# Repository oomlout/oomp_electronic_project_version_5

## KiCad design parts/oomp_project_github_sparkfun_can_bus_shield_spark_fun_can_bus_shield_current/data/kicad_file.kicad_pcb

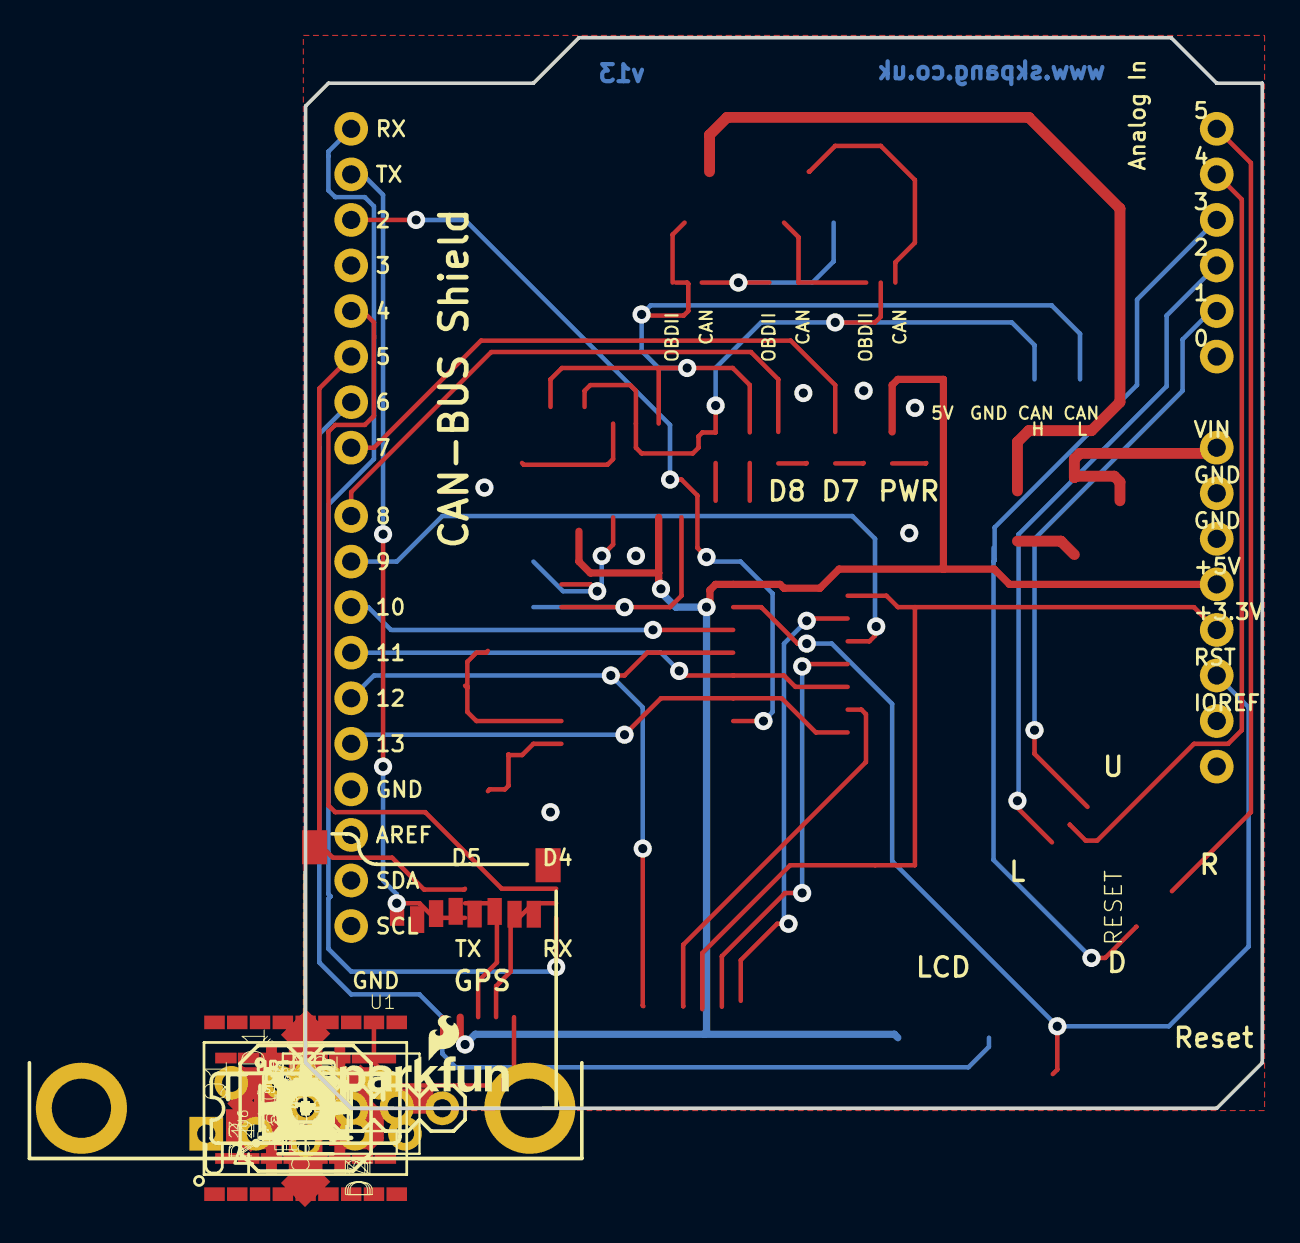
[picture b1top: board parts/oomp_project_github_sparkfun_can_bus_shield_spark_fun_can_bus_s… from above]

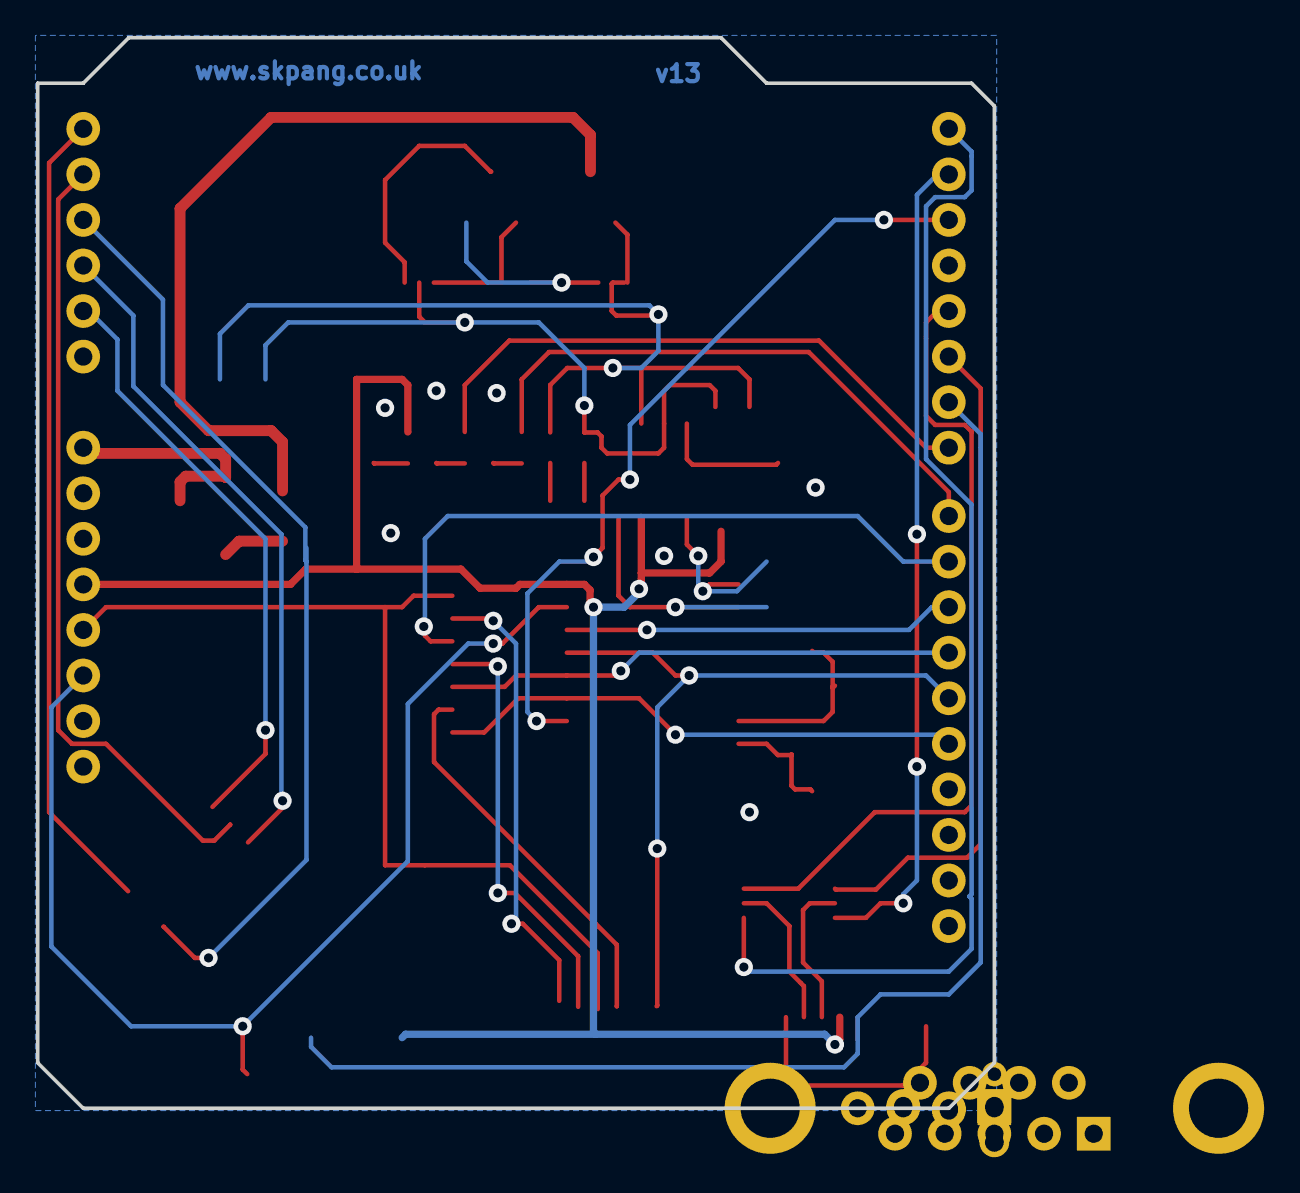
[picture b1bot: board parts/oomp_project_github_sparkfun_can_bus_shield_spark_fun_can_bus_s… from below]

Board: 2 copper layers, 53.3 x 59.7 mm, 48 parts (2 on the bottom side), 47 nets.

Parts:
C1, C6, C8: 0.1uF; 0603-CAP
C2, C3: 560pF; 0603-CAP
C4: 4.7uF; 0603-CAP
C5, C7: 22pF; 0603-CAP
C9: 1.0uF; 0603-CAP
D1: MBRA140; SMA-DIODE
D2, D3: GREEN; LED-0603
D4: RED; LED-0603
D5: PESD1CAN; SOT23-3
F1: PTC-1206
FRAME1: FRAME-LETTER; CREATIVE_COMMONS
FRAME2: FRAME-LETTERNO_PACKAGE; DUMMY
JP1: DNP; MOLEX-1X3_LOCK
JP2, JP3: FIDUCIAL1X2; FIDUCIAL-1X2
JP4: SFE_LOGO_NAME_FLAME.1_INCH; SFE_LOGO_NAME_FLAME_.1
JP5: DNP; 1X04
LOGO1: OSHW-LOGOM; OSHW-LOGO-M
Q1: 16MHz; CRYSTAL-SMD-5X3
R1, R2, R3: 1K; 0603-RES
R10, R12: 100; 0603-RES
R13: 4.7K; 0603-RES
S2: RESET; TACTILE-SWITCH-SMD
SJ1, SJ2, SJ4, SJ5, SJ6: JUMPER-PAD-3-2OF3_NC_BY_TRACE_SMALL; PAD-JUMPER-3-2OF3_NC_BY_TRACE_YES_SILK_FULL_BOX
SJ3: JUMPER-PAD-2-NC_BY_TRACE; PAD-JUMPER-2-NC_BY_TRACE_YES_SILK
TP1, TP2: TEST-POINT3X5; PAD.03X.05
U1: USD-SOCKET; MICROSD_1_1
U2: ARDUINO_R3_SHIELD; UNO_R3_SHIELD
U3: JST_VERTICAL; JST-6-SMD-VERT-1.0MM
U4: MCP2515; SO-18W
U5: MCP2551; SO08
U6: HEX_CONVERTER; SO016
U7: JOYSTICK_MINI
U$1: REVISION
X1: DB9 Plug; DB9_MALE

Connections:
3.3V: C8.2, C9.1, U1.4, U2.3.3V, U6.1
5V: C1.2, C6.2, D4.A, JP1.1, JP5.1, U2.5V, U3.2, U4.18, U5.3
12V: C4.1, D1.C, U2.VIN
CANH: D5.1, JP5.3, R12.2, SJ4.2, U5.7
CANL: D5.2, JP5.4, R10.2, SJ6.2, U5.6
CAN_CS: U2.D10, U4.16
CAN_INT: U2.D2, U4.12
CAN_RXD: TP1.P$1, U4.2, U5.4
CAN_TXD: TP2.P$1, U4.1, U5.1
D4: SJ2.3, U2.D4
D5: SJ1.3, U2.D5
GND: C1.1, C2.1, C3.1, C4.2, C5.1, C6.1, C7.1, C8.1, C9.2, D5.3, JP1.2, JP5.2, R1.1, R2.1, R3.1, R13.1, S2.1, SJ3.2, SJ5.2, U1.6, U1.CD1, U1.CD2, U1.GND1, U1.GND3, U2.GND@0, U2.GND@1, U2.GND@2, U3.1, U4.9, U5.2, U6.8, U7.GND
JOY-CLICK: U2.A4, U7.CTR
JOY-DOWN: U2.A3, U7.D
JOY-LEFT: U2.A2, U7.C
JOY-RIGHT: U2.A5, U7.B
JOY-UP: U2.A1, U7.A
LCD: JP1.3, U2.D6
LED1: D2.A, U2.D8
LED2: D3.A, U2.D7
MISO: U1.7, U2.D12, U4.15
MOSI: U2.D11, U4.14, U6.5
unnamed: SJ3.1, U3.5
unnamed: SJ6.3, X1.5
unnamed: D4.C, R1.2
unnamed: D2.C, R2.2
unnamed: D3.C, R3.2
unnamed: C2.2, R10.1
unnamed: C3.2, R12.1
unnamed: F1.2, X1.9
unnamed: R13.2, U5.8
unnamed: U1.2, U6.2
unnamed: D1.A, F1.1
unnamed: C7.2, Q1.3, U4.8
unnamed: C5.2, Q1.1, U4.7
unnamed: U1.3, U6.4
unnamed: SJ1.2, U3.3
unnamed: SJ2.2, U3.4
unnamed: U1.5, U6.6
PIN2: SJ5.3, SJ6.1, X1.2
PIN3: SJ4.3, SJ5.1, X1.3
PIN7: SJ4.1, X1.7
RS: S2.3, U2.RES, U4.17
RX: SJ2.1, U2.RX
SCK: U2.D13, U4.13, U6.7
SD_CS: U2.D9, U6.3
TX: SJ1.1, U2.TX

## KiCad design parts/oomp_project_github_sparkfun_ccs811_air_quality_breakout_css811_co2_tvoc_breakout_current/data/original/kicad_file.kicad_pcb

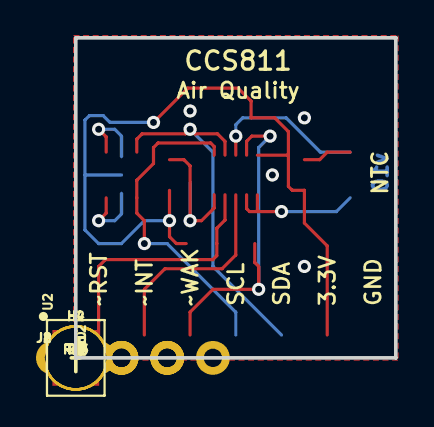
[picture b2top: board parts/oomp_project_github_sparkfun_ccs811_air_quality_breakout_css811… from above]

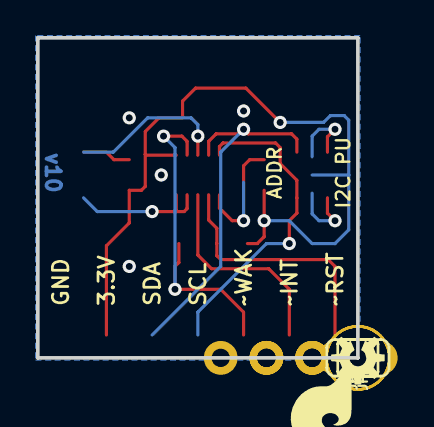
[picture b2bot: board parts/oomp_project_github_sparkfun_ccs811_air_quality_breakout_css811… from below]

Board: 2 copper layers, 17.8 x 17.8 mm, 20 parts (4 on the bottom side), 12 nets.

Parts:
C2: 1.0uF; 0603
FD1, FD2: FIDUCIAL1X2; FIDUCIAL-1X2
FRAME1: FRAME-LETTER; CREATIVE_COMMONS
H2, H4: STAND-OFF
J2: 1X03_NO_SILK
J8: 1X04_NO_SILK
JP1: SMT-JUMPER_3_2-NC_TRACE_SILK
JP2: SMT-JUMPER_2_NO_SILK
LOGO1: SFE_LOGO_FLAME.2_INCH; SFE_LOGO_FLAME_.2
LOGO4: OSHW-LOGOS; OSHW-LOGO-S
R1, R6: 100k; 0603
R2, R13, R14: 4.7k; 0603
R10: 10k; 0603
R12: 10k; AXIAL-0.1
U2: CCS811; LGA10

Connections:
3.3V: C2.1, J8.2, JP1.2, R2.2, R6.2, R10.2, U2.6
AUX: R10.1, R12.P$1, U2.8
CCS811_ADDR: JP2.2, R6.1, U2.1
GND: C2.2, J8.1, JP2.1, R1.1, U2.EP
unnamed: JP1.3, R13.2
unnamed: JP1.1, R14.2
NTC_SENSE: R12.P$2, U2.4, U2.5
SCL: J8.4, R14.1, U2.10
SDA: J8.3, R13.1, U2.9
~INT: J2.2, U2.3
~RST: J2.3, R2.1, U2.2
~WAKE: J2.1, R1.2, U2.7

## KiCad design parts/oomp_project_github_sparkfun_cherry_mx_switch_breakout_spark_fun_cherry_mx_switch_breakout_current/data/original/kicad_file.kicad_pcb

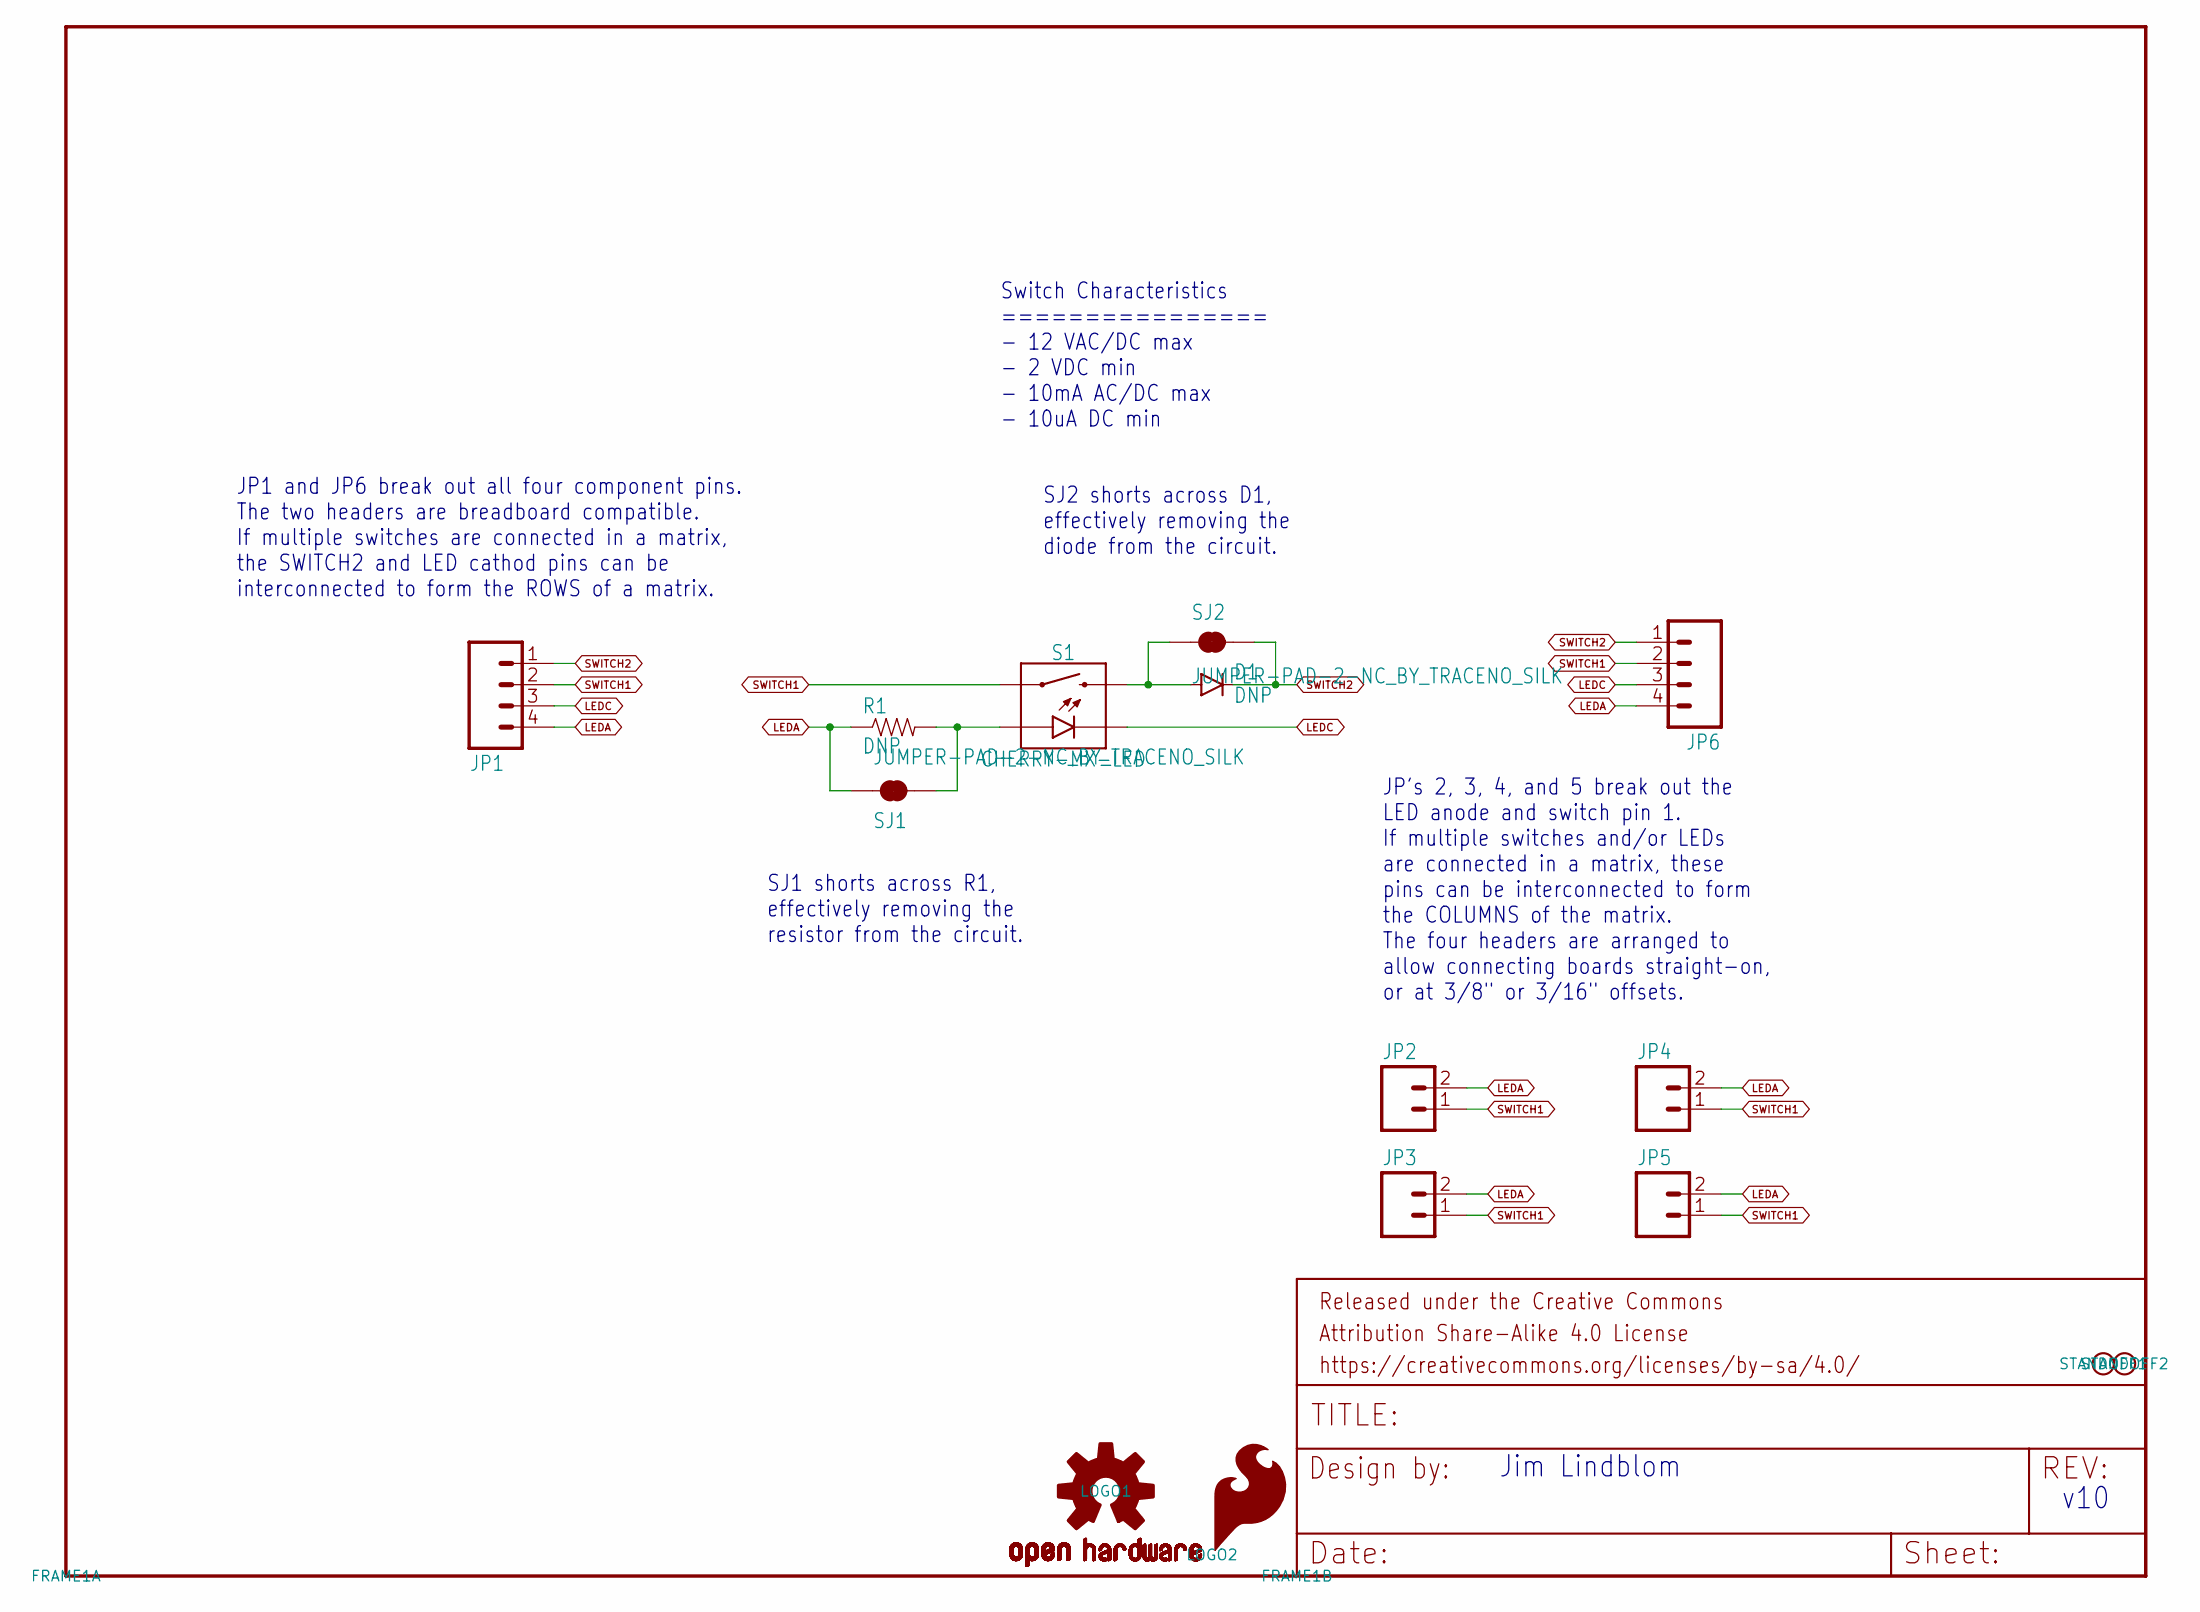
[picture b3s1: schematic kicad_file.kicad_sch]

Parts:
D1: DNP; DIODE-PTH-0.1
FRAME1: FRAME-LETTER; CREATIVE_COMMONS
JP1, JP6: M04NO_SILK_ALL_ROUND; 1X04_NO_SILK_ALL_ROUND
JP2, JP3, JP4, JP5: M021X02_NO_SILK; 1X02_NO_SILK
LOGO1: OSHW-LOGOS; OSHW-LOGO-S
LOGO2: SFE_LOGO_FLAME.1_INCH; SFE_LOGO_FLAME_.1
R1: DNP; AXIAL-0.1
S1: CHERRY-MX-LED
SJ1, SJ2: JUMPER-PAD-2-NC_BY_TRACENO_SILK; PAD-JUMPER-2-NC_BY_TRACE_NO_SILK
STANDOFF1, STANDOFF2: STAND-OFF2-56; STAND-OFF-2-56

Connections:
LEDA: JP1.4, JP2.2, JP3.2, JP4.2, JP5.2, JP6.4, R1.P$1 (1), SJ1.1
LEDC: JP1.3, JP6.3, S1.K (C)
unnamed: R1.P$2 (2), S1.A, SJ1.2
unnamed: D1.A, S1.S2, SJ2.1
SWITCH1: JP1.2, JP2.1, JP3.1, JP4.1, JP5.1, JP6.2, S1.S1
SWITCH2: D1.C, JP1.1, JP6.1, SJ2.2

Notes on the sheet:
Switch Characteristics ================ - 12 VAC/DC max - 2 VDC min - 10mA AC/DC max - 10uA DC min
v10
SJ2 shorts across D1, effectively removing the diode from the circuit.
Jim Lindblom
SJ1 shorts across R1, effectively removing the resistor from the circuit.
JP's 2, 3, 4, and 5 break out the LED anode and switch pin 1. If multiple switches and/or LEDs are connected in a matrix, these pins can be interconnected to form the COLUMNS of the matrix. The four headers are arranged to allow connecting boards straight-on, or at 3/8" or 3/16" offsets.
JP1 and JP6 break out all four component pins. The two headers are breadboard compatible. If multiple switches are connected in a matrix, the SWITCH2 and LED cathod pins can be interconnected to form the ROWS of a matrix.

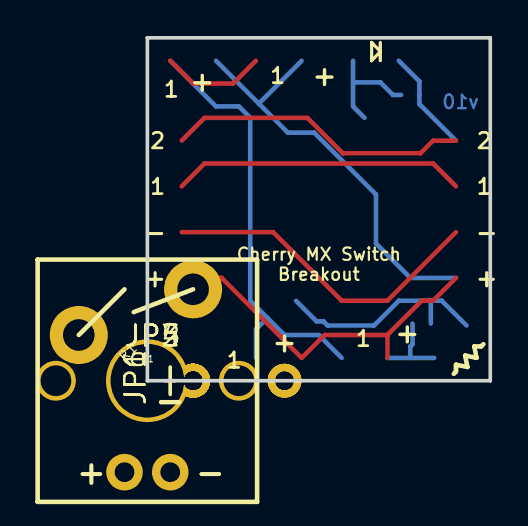
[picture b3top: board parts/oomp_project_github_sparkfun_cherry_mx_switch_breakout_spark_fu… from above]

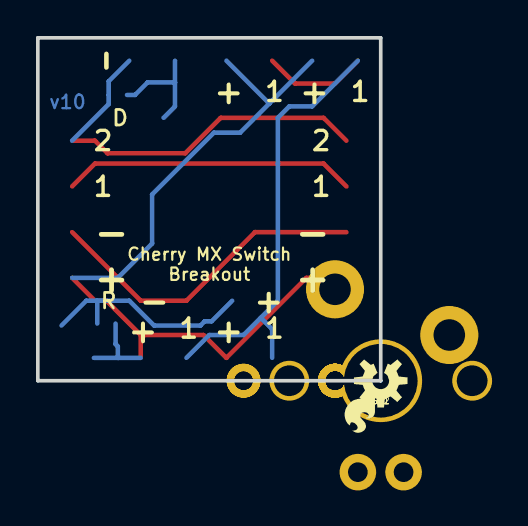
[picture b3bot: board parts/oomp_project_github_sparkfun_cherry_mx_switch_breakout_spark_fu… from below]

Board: 2 copper layers, 19.1 x 19.1 mm, 16 parts (4 on the bottom side), 6 nets.

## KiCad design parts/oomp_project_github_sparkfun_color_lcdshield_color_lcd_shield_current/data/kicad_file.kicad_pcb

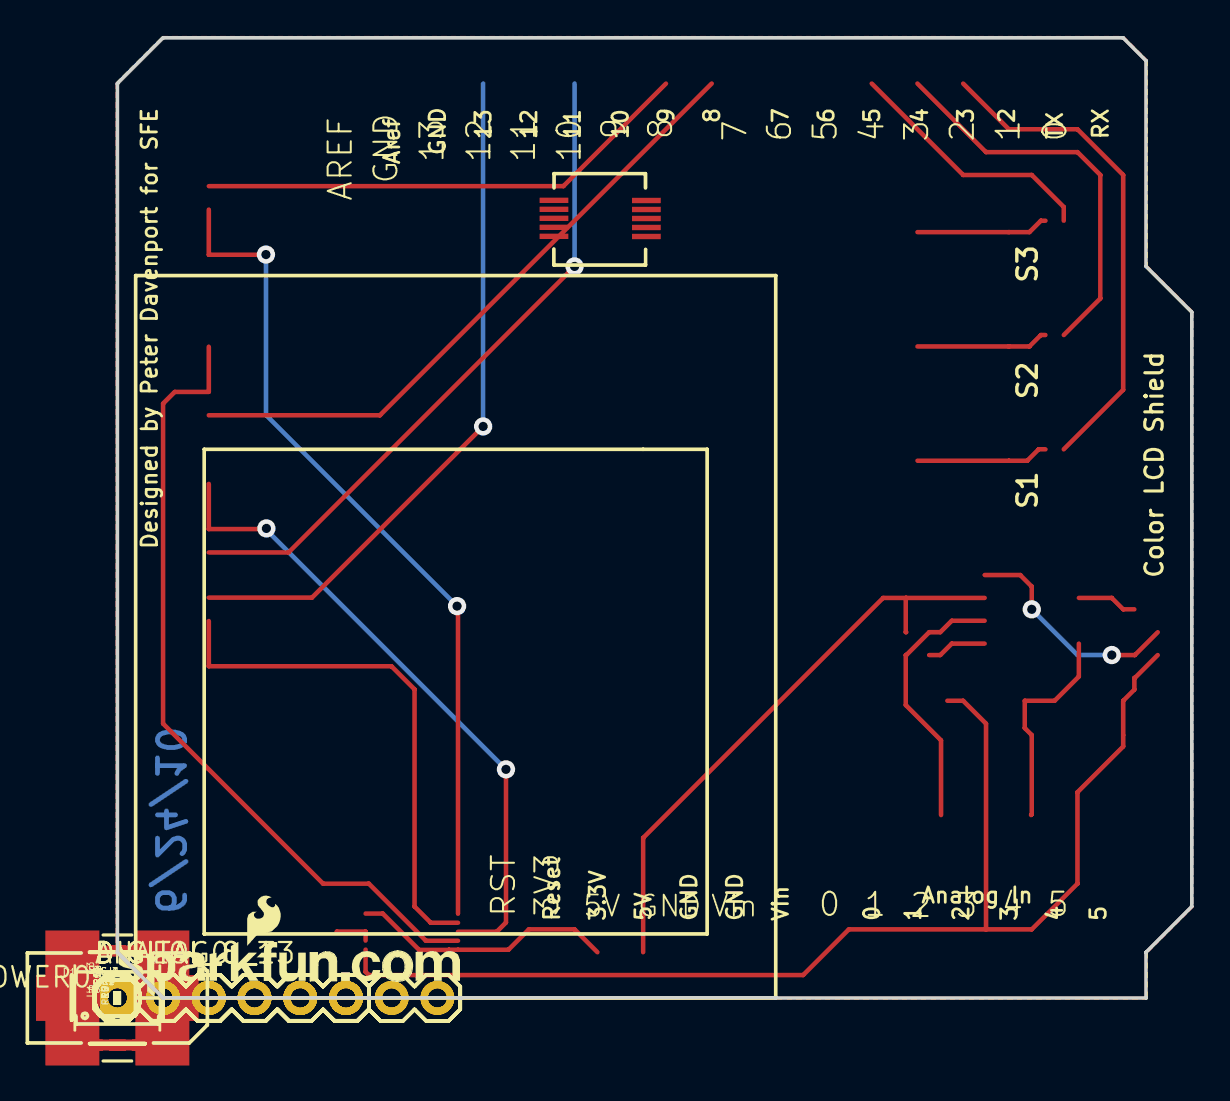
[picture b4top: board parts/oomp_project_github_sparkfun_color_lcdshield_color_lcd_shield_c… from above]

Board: 2 copper layers, 59.7 x 53.3 mm, 32 parts (0 on the bottom side), 23 nets.

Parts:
ANALOG0: 1X06
C1: 1nF; 0402-CAP
C2: .1uF; 0402-CAP
C3: 100uF; EIA7343
D1: MBRA140; SMA-DIODE
DIGITAL_0_7, DIGITAL_8_13: 1X08
JP1: LOGO-SFENEW; SFE-NEW-WEBLOGO
JP2, JP3: FIDUCIAL1X2; FIDUCIAL-1X2
L1: 220uH; NPI75C
POWER0: 1X06
R1, R5, R7, R9, R11: 3.3k; 0402-RES
R2: 15k; 0402-RES
R3: 180; 0402-RES
R4: .27; 0402-RES
R6, R8, R10, R12: 1.8k; 0402-RES
S1, S3, S4: TACTILE_SWITCH_SMD
SJ1, SJ2, SJ3: SOLDERJUMPERTRACE; SJ_2S-TRACE
U1: MC34063SMD; SO08
U$1: NOKIA6100_LCD

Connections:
3.3V: POWER0.5, U$1.1, U$1.6
5V: POWER0.4, R4.1, U1.6
CS: R5.2, R6.1, U$1.5
D3: DIGITAL_0_7.5, SJ2.2
D4: DIGITAL_0_7.4, SJ1.2
D5: DIGITAL_0_7.3, SJ3.2
D8: DIGITAL_8_13.8, R8.2
D9: DIGITAL_8_13.7, R6.2
D11: DIGITAL_8_13.5, R10.2
D13: DIGITAL_8_13.3, R12.2
DIO: R9.2, R10.1, U$1.3
GND: C1.2, C2.2, C3.C, DIGITAL_8_13.2, POWER0.2, POWER0.3, R1.1, R5.1, R7.1, R9.1, R11.1, S1.1, S1.2, S3.1, S3.2, S4.1, S4.2, U1.2, U1.4, U$1.8, U$1.9
LCD-RESET: R7.2, R8.1, U$1.2
unnamed: S1.3, S1.4, SJ3.1
unnamed: S3.3, S3.4, SJ1.1
unnamed: S4.3, S4.4, SJ2.1
unnamed: R1.2, R2.1, U1.5
unnamed: C1.1, U1.3
unnamed: D1.A, L1.1, U1.1
unnamed: R3.1, U1.8
unnamed: L1.2, R3.2, R4.2, U1.7
SCK: R11.2, R12.1, U$1.4
VLED: C2.1, C3.A, D1.C, R2.2, U$1.10

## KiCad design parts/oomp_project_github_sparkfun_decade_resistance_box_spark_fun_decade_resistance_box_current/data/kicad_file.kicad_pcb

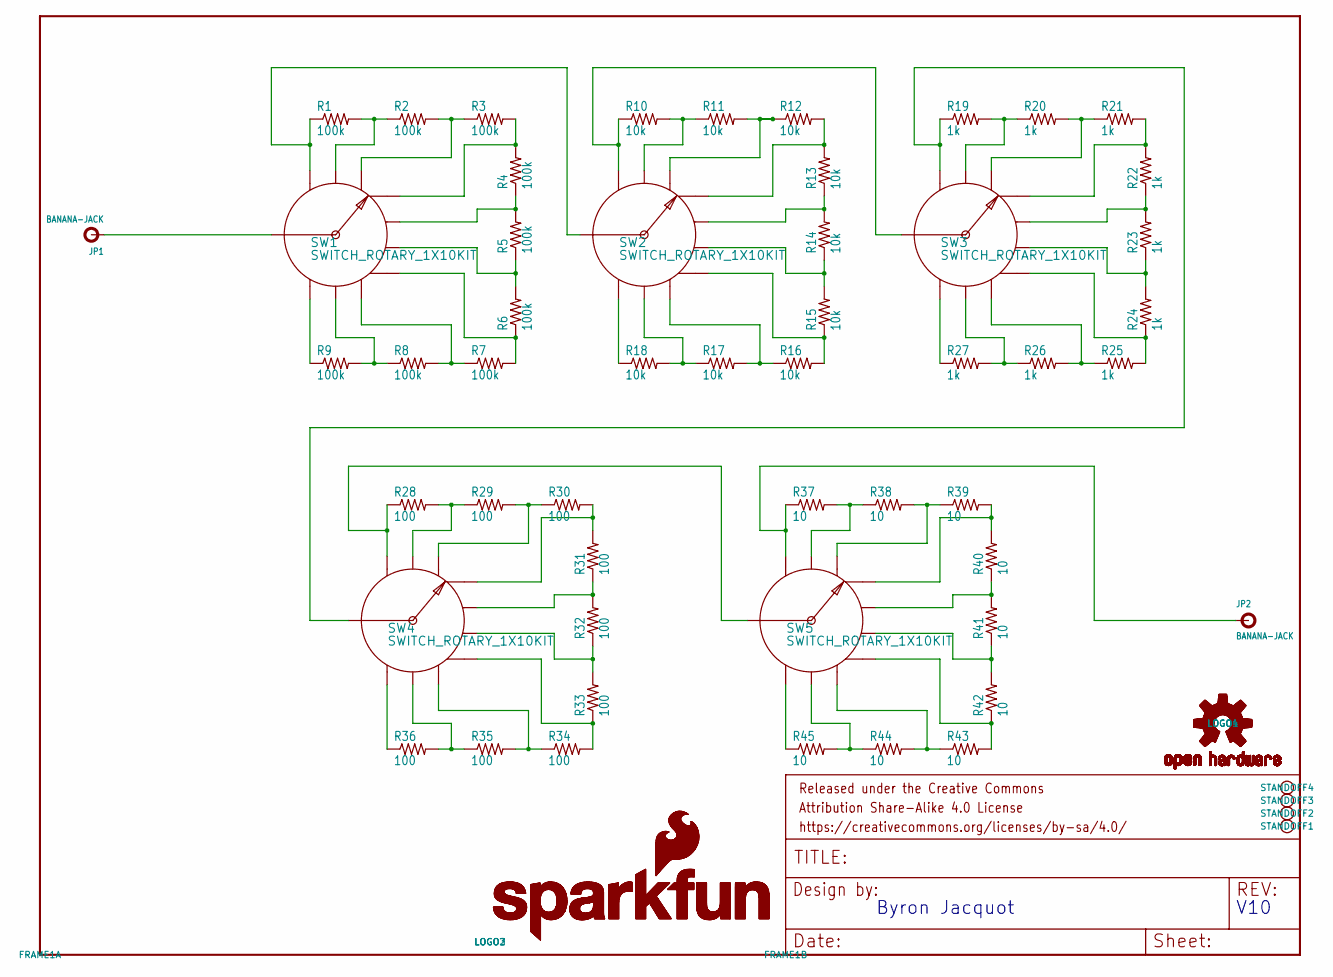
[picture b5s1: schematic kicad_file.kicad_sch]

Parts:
FRAME1: FRAME-LETTER; CREATIVE_COMMONS
JP1, JP2: BANANA-JACK
LOGO1, LOGO4: OSHW-LOGOL; OSHW-LOGO-L
LOGO2: SFE_LOGO_NAME_FLAME.2_INCH; SFE_LOGO_NAME_FLAME_.2
LOGO3: SFE_LOGO_NAME_FLAME.5_INCH; SFE_LOGO_NAME_FLAME_.5
R1, R2, R3, R4, R5, R6, R7, R8, R9: 100k; AXIAL-0.1EZ
R10, R11, R12, R13, R14, R15, R16, R17, R18: 10k; AXIAL-0.1EZ
R19, R20, R21, R22, R23, R24, R25, R26, R27: 1k; AXIAL-0.1EZ
R28, R29, R30, R31, R32, R33, R34, R35, R36: 100; AXIAL-0.1EZ
R37, R38, R39, R40, R41, R42, R43, R44, R45: 10; AXIAL-0.1EZ
STANDOFF1, STANDOFF2, STANDOFF3, STANDOFF4: STAND-OFF
SW1, SW2, SW3, SW4, SW5: SWITCH_ROTARY_1X10KIT; ROTARY_SWITCH_1X10_KIT

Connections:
unnamed: R1.P$1 (1), SW1.1, SW2.COMMON
unnamed: R1.P$2 (2), R2.P$1 (1), SW1.2
unnamed: R2.P$2 (2), R3.P$1 (1), SW1.3
unnamed: R3.P$2 (2), R4.P$2 (2), SW1.4
unnamed: R4.P$1 (1), R5.P$2 (2), SW1.5
unnamed: R5.P$1 (1), R6.P$2 (2), SW1.6
unnamed: R6.P$1 (1), R7.P$2 (2), SW1.7
unnamed: R7.P$1 (1), R8.P$2 (2), SW1.8
unnamed: R8.P$1 (1), R9.P$2 (2), SW1.9
unnamed: R9.P$1 (1), SW1.10
unnamed: R10.P$1 (1), SW2.1, SW3.COMMON
unnamed: R10.P$2 (2), R11.P$1 (1), SW2.2
unnamed: R11.P$2 (2), R12.P$1 (1), SW2.3
unnamed: R12.P$2 (2), R13.P$2 (2), SW2.4
unnamed: R13.P$1 (1), R14.P$2 (2), SW2.5
unnamed: R14.P$1 (1), R15.P$2 (2), SW2.6
unnamed: JP1.P$1, SW1.COMMON
unnamed: R15.P$1 (1), R16.P$2 (2), SW2.7
unnamed: R16.P$1 (1), R17.P$2 (2), SW2.8
unnamed: R17.P$1 (1), R18.P$2 (2), SW2.9
unnamed: R18.P$1 (1), SW2.10
unnamed: R19.P$1 (1), SW3.1, SW4.COMMON
unnamed: R19.P$2 (2), R20.P$1 (1), SW3.2
unnamed: R20.P$2 (2), R21.P$1 (1), SW3.3
unnamed: R21.P$2 (2), R22.P$2 (2), SW3.4
unnamed: R22.P$1 (1), R23.P$2 (2), SW3.5
unnamed: R23.P$1 (1), R24.P$2 (2), SW3.6
unnamed: R24.P$1 (1), R25.P$2 (2), SW3.7
unnamed: R25.P$1 (1), R26.P$2 (2), SW3.8
unnamed: R26.P$1 (1), R27.P$2 (2), SW3.9
unnamed: R27.P$1 (1), SW3.10
unnamed: R28.P$1 (1), SW4.1, SW5.COMMON
unnamed: R28.P$2 (2), R29.P$1 (1), SW4.2
unnamed: R29.P$2 (2), R30.P$1 (1), SW4.3
unnamed: R30.P$2 (2), R31.P$2 (2), SW4.4
unnamed: R31.P$1 (1), R32.P$2 (2), SW4.5
unnamed: R32.P$1 (1), R33.P$2 (2), SW4.6
unnamed: R33.P$1 (1), R34.P$2 (2), SW4.7
unnamed: R34.P$1 (1), R35.P$2 (2), SW4.8
unnamed: R35.P$1 (1), R36.P$2 (2), SW4.9
unnamed: R36.P$1 (1), SW4.10
unnamed: JP2.P$1, R37.P$1 (1), SW5.1
unnamed: R37.P$2 (2), R38.P$1 (1), SW5.2
unnamed: R38.P$2 (2), R39.P$1 (1), SW5.3
unnamed: R39.P$2 (2), R40.P$2 (2), SW5.4
unnamed: R40.P$1 (1), R41.P$2 (2), SW5.5
unnamed: R41.P$1 (1), R42.P$2 (2), SW5.6
unnamed: R42.P$1 (1), R43.P$2 (2), SW5.7
unnamed: R43.P$1 (1), R44.P$2 (2), SW5.8
unnamed: R44.P$1 (1), R45.P$2 (2), SW5.9
unnamed: R45.P$1 (1), SW5.10

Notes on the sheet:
V10
Byron Jacquot

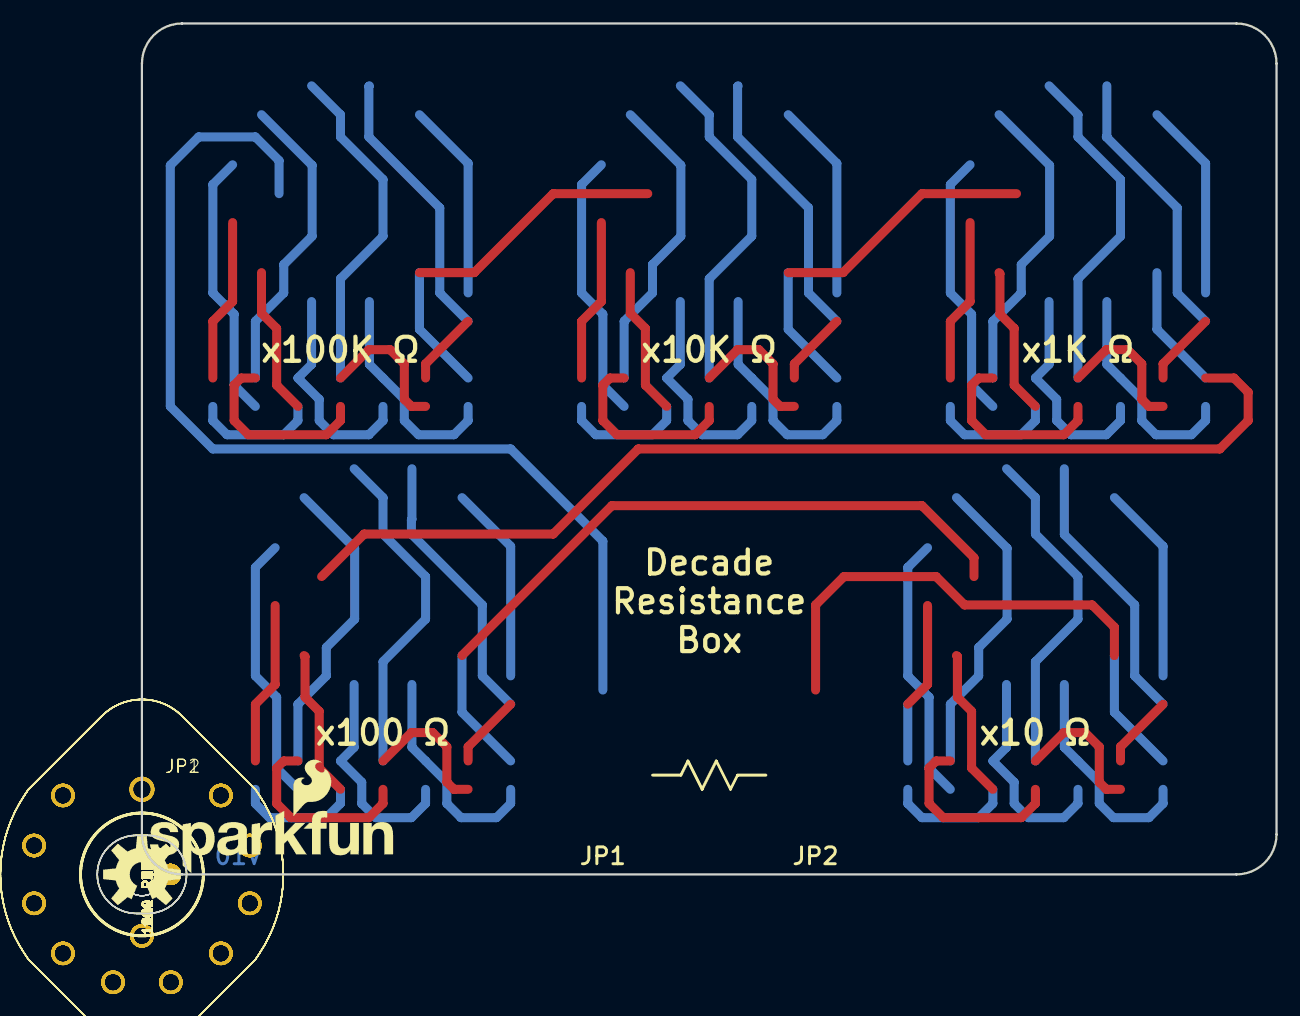
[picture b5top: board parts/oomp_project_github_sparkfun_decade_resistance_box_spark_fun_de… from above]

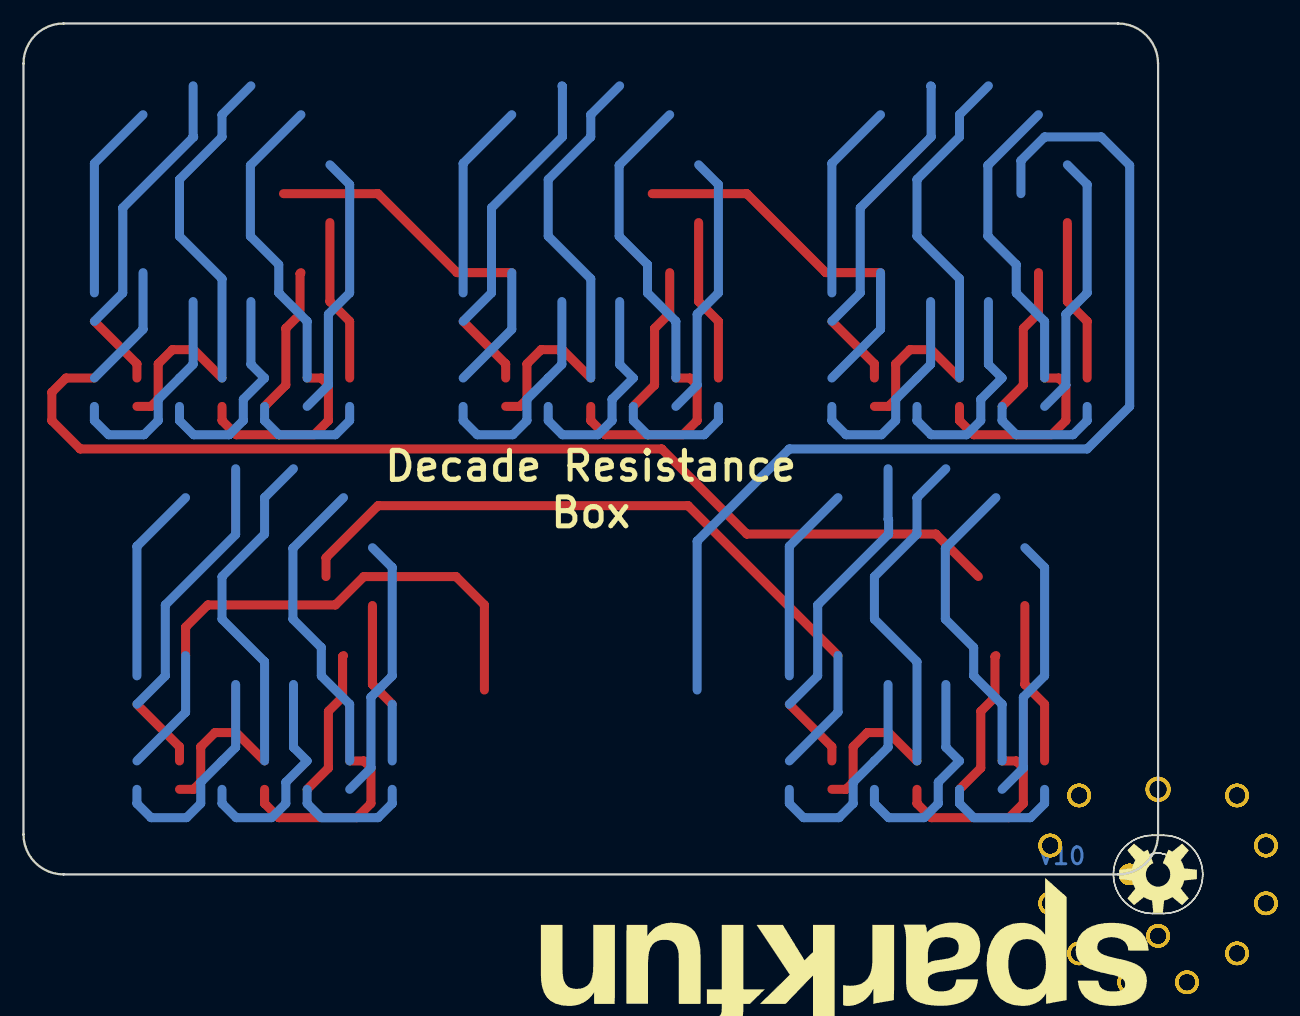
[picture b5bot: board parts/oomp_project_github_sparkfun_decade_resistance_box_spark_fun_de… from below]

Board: 2 copper layers, 105.6 x 79.7 mm, 66 parts (2 on the bottom side), 51 nets.

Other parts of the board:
UNK_HOLE_0: dummyfp0
UNK_HOLE_1: dummyfp1
UNK_HOLE_2: dummyfp2
UNK_HOLE_3: dummyfp3
UNK_HOLE_4: dummyfp4

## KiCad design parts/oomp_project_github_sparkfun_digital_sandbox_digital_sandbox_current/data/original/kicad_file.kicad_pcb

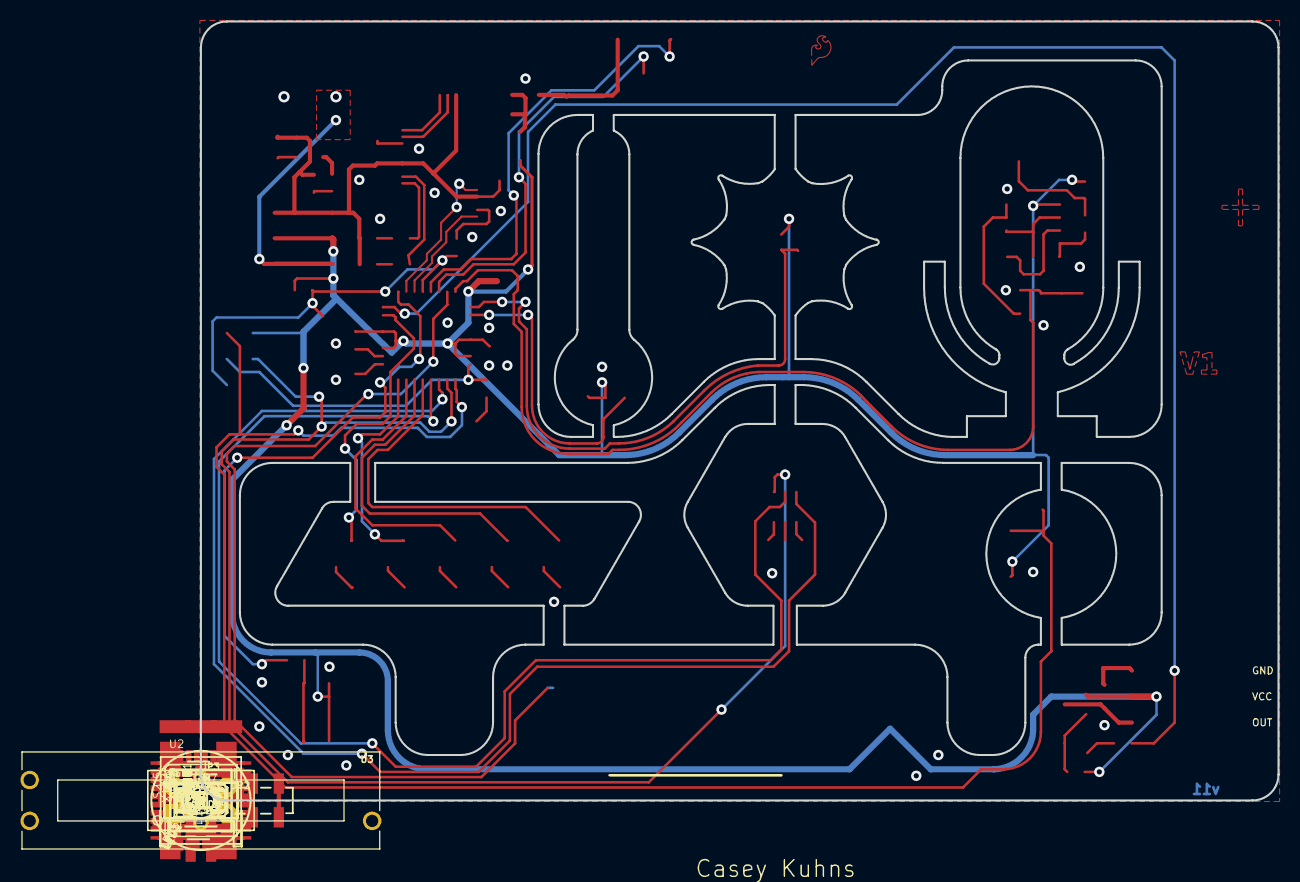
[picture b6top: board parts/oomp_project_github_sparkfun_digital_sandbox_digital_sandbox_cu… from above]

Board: 2 copper layers, 105.4 x 76.2 mm, 80 parts (0 on the bottom side), 59 nets.

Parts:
C1, C6, C7, C8, C10, C11, C12, C13, C14: 0.1uF; 0603-CAP
C2, C5: 4.7uF; 0603-CAP
C3: 47uF; EIA3528
C4: 1.0uF; 0603-CAP
C9: 10uF; EIA3216
D1: Yellow; LED-0603
D2: RED; LED-1206
D4, D5: SOD-323
F1, F2: PTCSMD; PTC-1206
FID1, FID2: FIDUCIAL1X2; FIDUCIAL-1X2
FRAME1: FRAME-LEDGER; CREATIVE_COMMONS
J1: AVR_SPI_PRG_6NS; 2X3-NS
JP1: LiPo; JST-2-SMD
JP2: 1x3 RA Female .1"; 1X03_SMD_RA_FEMALE
JP3: 1X04_SMD_STRAIGHT_COMBO
LED1, LED2, LED3, LED4, LED5: White; LED-1206
LED6: Red; LED-0603
LED7: Green; LED-0603
Q1: MOSFET-N; SOT23
Q2: MOSFET-P; SOT23-3
R1, R5: 330; 0603-RES
R2, R3, R4, R14, R23, R24, R26, R27: 10k; 0603-RES
R6, R7, R13, R15: 1k; 0603-RES
R8, R9, R10, R11, R12, R17: 300; 0603-RES
R19, R21: 100; 0603-RES
R22: 100k; 0603-RES
R25: 2.2k; 0603-RES
S1: Reset; TACTILE_SWITCH_SMD
S2: AYZ0202
S3: On/Off; AYZ0202
S5: SWITCH-MOMENTARY-2SMD-4; TACTILE_SWITCH_TALL
STANDOFF1, STANDOFF2, STANDOFF3, STANDOFF4: STAND-OFF
U1: MCP73831; SOT23-5
U2: ATMEGA328; TQFP32-08
U3: 10K_LINEAR_SLIDE_POT_SMALL; C2031N-1A2-B10K-GP
U4: MCP9700; SOT23-3
U5: FT232RLSSOP; SSOP28DB
U6: LIGHTSENSORALS; ALS-PT19
U7: V_REG_MIC52053.3V; SOT23-5
U8: LMV358SOIC; SO08
U9: MIC9.7MM; MIC-9.7MM
U$5: LED-TRICOLOR; PLCC-6-LED
X1: USBSMD; USB-MINIB
Y1: 8MHz; RESONATOR-SMD

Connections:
3.3V: C10.1, U5.17
5V: C2.1, C7.1, C9.A, D1.A, R13.2, R15.2, S3.3, S3.6, U1.4, U5.4, U5.20, X1.VBUS
A0: U2.23, U4.2
A1: R14.1, U2.24, U6.E
A2: C12.2, C13.2, D4.C, R22.1, U2.25
A3: U2.26, U3.1
A4: JP3.3, U2.27
A5: JP3.4, U2.28
BLUE: R17.2, U$5.CB
D2: R3.2, U2.32
D3: R6.2, U2.1
D4: LED1.A, U2.2
D5: LED2.A, U2.9
D6: LED3.A, U2.10
D7: LED4.A, U2.11
D8: LED5.A, U2.12
D9: U2.13, U$5.AR
D10: U2.14, U$5.AG
D11: J1.4, U2.15, U$5.AB
D12: J1.1, R23.2, S5.A2, U2.16
D13: J1.3, R5.2, U2.17
DTR: C1.1, U5.2
GND: C2.2, C3.C, C4.2, C5.2, C6.2, C7.2, C8.2, C9.C, C10.2, C11.2, C12.1, C13.1, D2.C, F1.1, J1.6, JP1.1, JP3.1, Q1.2, R4.1, R8.2, R9.2, R10.2, R11.2, R12.2, R14.2, R17.1, R19.1, R21.1, R22.2, R23.1, R25.2, R26.1, S1.3, S1.4, S2.1, S2.4, U1.2, U2.3, U2.5, U2.21, U3.2, U4.3, U5.7, U5.18, U5.21, U5.25, U5.26, U7.2, U8.4, U9.2, X1.GND, Y1.2
GRN: R21.2, U$5.CG
unnamed: U2.7, Y1.1
unnamed: D2.A, R5.1
unnamed: U2.8, Y1.3
unnamed: Q1.3, Q2.1, R7.2
unnamed: LED6.A, R13.1
unnamed: LED7.A, R15.1
unnamed: F2.1, U7.1, U7.3
unnamed: D5.C, JP2.1, Q2.3
unnamed: LED3.C, R10.1
unnamed: Q1.1, R6.1
unnamed: LED4.C, R11.1
unnamed: C11.1, JP3.2, U7.5
unnamed: LED5.C, R12.1
unnamed: R3.1, S2.2, S2.5
unnamed: D5.A, F1.2, JP2.3
unnamed: C14.1, R27.1, U9.1
unnamed: LED1.C, R8.1
unnamed: C14.2, R26.2, U8.5
unnamed: LED2.C, R9.1
unnamed: R24.1, R25.1, U8.6
unnamed: D4.A, U8.1, U8.2
unnamed: R24.2, U8.3, U8.7
unnamed: D1.C, R1.1
PROG: R4.2, U1.5
RED: R19.2, U$5.CR
RST: C1.2, J1.5, R2.1, S1.1, U2.29
RXD: U2.30, U5.1
RXLED: LED7.C, U5.22
STAT: R1.2, U1.1
TXD: U2.31, U5.5
TXLED: LED6.C, U5.23
USB_D+: U5.15, X1.D+
USB_D-: U5.16, X1.D-
VBATT: C5.1, JP1.2, S3.1, S3.4, U1.3
VCC: C3.A, C4.1, C6.1, C8.1, F2.2, J1.2, JP2.2, Q2.2, R2.2, R7.1, R27.2, S2.3, S2.6, S3.2, S3.5, S5.B2, U2.4, U2.6, U2.18, U2.20, U3.3, U4.1, U6.C, U8.8

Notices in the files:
parts/oomp_project_github_sparkfun_can_bus_shield_spark_fun_can_bus_shield_current/data/original/kicad_file.kicad_sch:
Released under the Creative Commons
https://creativecommons.org/licenses/by-sa/4.0
parts/oomp_project_github_sparkfun_el_sequencer_el_sequencer_current/data/original/kicad_file.kicad_sch:
http://creativecommons.org/licenses/by-sa/3.0
parts and their libraries:
Released under the Creative Commons Attribution Share-Alike 4.0 License
Released under the Creative Commons Attribution Share-Alike 3.0 License
https://creativecommons.org/licenses/by-sa/3.0
